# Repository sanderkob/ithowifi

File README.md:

# ithowifi
ESP based WiFi controller for Itho devices

*(note: I'm in no way a professional hardware/software engineer and have no background in these subjects. I like this for a hobby, to learn and to share my projects)*

Finished boards can be ordered in my webshop:  
[https://www.nrgwatch.nl](http://www.nrgwatch.nl)  
or in my Tindie store:  
[https://www.tindie.com/products/19680/](https://www.tindie.com/products/19680/)  

|CVE Add-on|non-CVE wifi module|
|:---:|:---:|
|  |  |

## WiFi add-on to control itho central ventilation units

-   Control your* Itho Daalderop CVE with one simple add-on module
-   No hardware changes needed to the itho box, no warranty void
-   Control the speed setting of the fan from 0 - 254 through either a simple web-interface, MQTT or WebAPI (CVE models and HRU200 only)
-   Send remote commands without having a real remote (virtual remote function)
-   Easily integrate this wifi controller in any home domotica system through MQTT or WebAPI
-   Installation can be done in minutes
-   Detailed installation manual

###  CVE Models confirmed to work:
-   CVE ECO 2 (this unit is also sold by the brand 'Heatrae Sadia' in the uk)
-   CVE ECO RFT (SE/SP, HE/HP)
-   CVE-S ECO (SE/SP, HE/HP)
-   CVE-S OPTIMA package with built-in CO2 sensor. CO2 sensor usable but an extra long pinheader needs to be soldered on the add-on)
-   HRU 200 ECO (also sold as 'Elektrodesign EHR 140 Akor BP' and 'Heatrae Sadia Advance Plus')

###  NON-CVE Models confirmed to work:
-   HRU eco fan
-   HRU 350
-   DemandFlow
-   QualityFlow
-   HeatPump WPU
-   AutoTemp

###  Models confirmed to work but modifications needed:
-   HRU 300 - see: https://github.com/arjenhiemstra/ithowifi/issues/97

####   An important note about the firmware for CVE and HRU200 devices:
The cve add-on is able to control the itho unit in standard or medium mode setting only. This means you can use the original remote but if you leave the itho box in low or high setting the itho won't accept commands from the add-on. This is itho designed behaviour. Adding a CC1101 RF module and/or letting the add-on present itself as virtual remote can circumvent this issue, the virtual remote function can also be used to force a medium mode before sending commands.

## Hardware:

A sample hardware design (KiCad) is included, this module can be plugged on the Itho main PCB directly without extra components.
The design files and BOM can be found in the hardware folder.

## Further information:

More information is available on the wiki and in the manual:
|  |  |
|---|---|
|Wiki:  |https://github.com/arjenhiemstra/ithowifi/wiki  |
|Dutch:  |https://github.com/arjenhiemstra/ithowifi/raw/master/handleiding.pdf  |
|English:  |https://github.com/arjenhiemstra/ithowifi/raw/master/manual.pdf  |

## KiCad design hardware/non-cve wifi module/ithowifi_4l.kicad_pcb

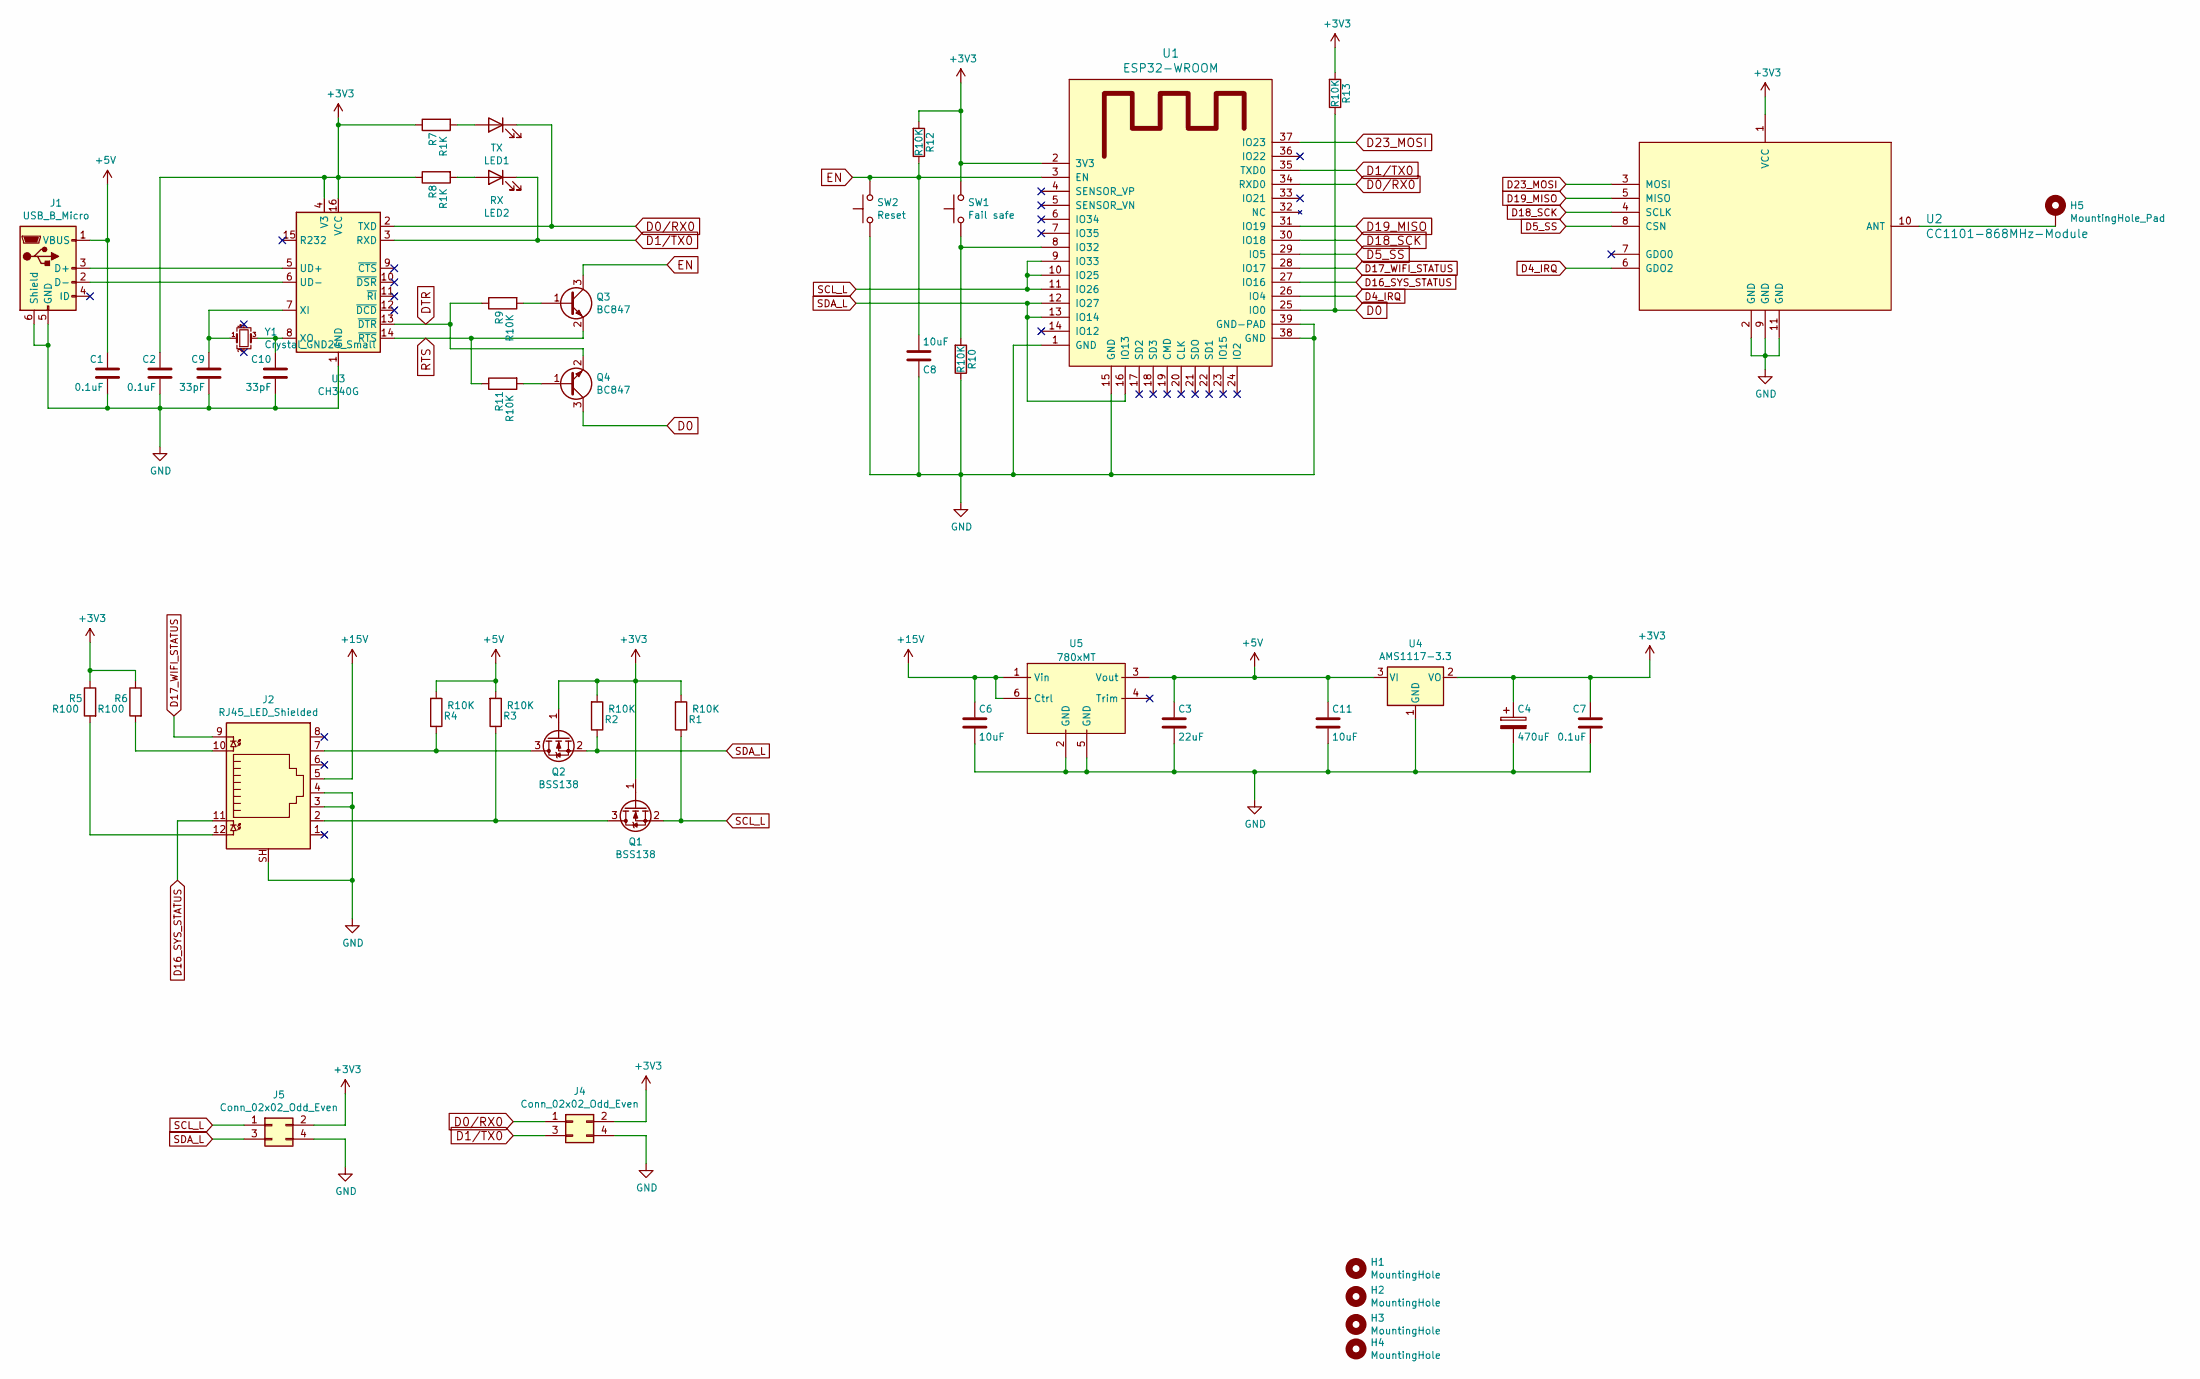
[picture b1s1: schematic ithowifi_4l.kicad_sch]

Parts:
C1, C2, C7: 0.1uF; C_0805_2012Metric
C3: 22uF; C_0805_2012Metric; LCSC C15850
C4: 470uF; CP_EIA-7343-31_Kemet-D; LCSC C7229
C6, C8, C11: 10uF; C_0805_2012Metric; LCSC C15850
C9, C10: 33pF; C_0805_2012Metric
H1, H2, H3, H4: MountingHole; MountingHole_2.5mm
H5: MountingHole_Pad; Pin_D1.0mm_L10.0mm
J1: USB_B_Micro; micro usb; LCSC C879723
J2: RJ45_LED_Shielded; RRJ45R08PC000; LCSC C386757
J4, J5: Conn_02x02_Odd_Even; PinHeader_2x02_P2.54mm_Vertical
LED1: TX; LED_0805_2012Metric; LCSC C2293
LED2: RX; LED_0805_2012Metric; LCSC C2293
Q1, Q2: BSS138; SOT-23W; LCSC C170166
Q3, Q4: BC847; SOT-23W; LCSC C6749
R1, R2, R3, R4, R9, R10, R11, R12, R13: R10K; R_0805_2012Metric; LCSC C17414
R5, R6: R100; R_0805_2012Metric; LCSC C17408
R7, R8: R1K; R_0805_2012Metric; LCSC C17513
SW1: Fail safe; TS-1187; LCSC C92589
SW2: Reset; TS-1187; LCSC C92589
U1: ESP32-WROOM; ESP32-WROOM-32E; LCSC C473012
U2: CC1101-868MHz-Module
U3: CH340G; SOIC-16_3.9x9.9mm_P1.27mm
U4: AMS1117-3.3; SOT-223-3_TabPin2
U5: 780xMT; Mornsun 780xMT; LCSC C2684892
Y1: Crystal_GND24_Small; Crystal_SMD_TXC_7M-4Pin_3.2x2.5mm

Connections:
+3V3: C2.1, C4.1, C7.1, J4.2, J5.2, Q1.1 (G), Q2.1 (G), R1.2, R2.2, R5.1, R6.1, R7.1, R8.1, R12.2, R13.2, SW1.2, U1.2 (3V3), U2.1 (VCC), U3.4 (V3), U3.16 (VCC), U4.2 (VO)
+5V: C1.1, C3.1, C11.1, J1.1 (VBUS), R3.2, R4.2, U4.3 (VI), U5.3 (Vout)
+15V: C6.1, J2.5, U5.1 (Vin), U5.6 (Ctrl)
D0: Q4.3 (C), R13.1, U1.25 (IO0)
D0/RX0: J4.1, LED1.1 (K), U1.34 (RXD0), U3.2 (TXD)
D1/TX0: J4.3, LED2.1 (K), U1.35 (TXD0), U3.3 (RXD)
D4_IRQ: U1.26 (IO4), U2.6 (GDO2)
D5_SS: U1.29 (IO5), U2.8 (CSN)
D16_SYS_STATUS: J2.11, U1.27 (IO16)
D17_WIFI_STATUS: J2.9, U1.28 (IO17)
D18_SCK: U1.30 (IO18), U2.4 (SCLK)
D19_MISO: U1.31 (IO19), U2.5 (MISO)
D23_MOSI: U1.37 (IO23), U2.3 (MOSI)
DTR: Q4.2 (E), R9.1, U3.13 (~DTR)
EN: C8.2, Q3.3 (C), R12.1, SW2.2, U1.3 (EN)
GND: C1.2, C2.2, C3.2, C4.2, C6.2, C7.2, C8.1, C9.2, C10.2, C11.2, J1.5 (GND), J1.6 (Shield), J2.3, J2.4, J2.SH, J4.4, J5.4, R10.1, SW2.1, U1.1 (GND), U1.15 (GND), U1.38 (GND), U1.39 (GND-PAD), U2.2 (GND), U2.9 (GND), U2.11 (GND), U3.1 (GND), U4.1 (GND), U5.2 (GND), U5.5 (GND)
unnamed: C9.1, U3.7 (XI), Y1.1
unnamed: C10.1, U3.8 (XO), Y1.3
unnamed: H5.1, U2.10 (ANT)
unnamed: J1.2 (D-), U3.6 (UD-)
unnamed: J1.3 (D+), U3.5 (UD+)
unnamed: J2.2, Q1.3 (D), R3.1
unnamed: J2.7, Q2.3 (D), R4.1
unnamed: J2.10, R6.2
unnamed: J2.12, R5.2
unnamed: LED1.2 (A), R7.2
unnamed: LED2.2 (A), R8.2
unnamed: Q3.1 (B), R9.2
unnamed: Q4.1 (B), R11.2
unnamed: R10.2, SW1.1, U1.8 (IO32)
RTS: Q3.2 (E), R11.1, U3.14 (~RTS)
SCL_L: J5.1, Q1.2 (S), R1.1, U1.9 (IO33), U1.10 (IO25), U1.11 (IO26)
SDA_L: J5.3, Q2.2 (S), R2.1, U1.12 (IO27), U1.13 (IO14), U1.16 (IO13)

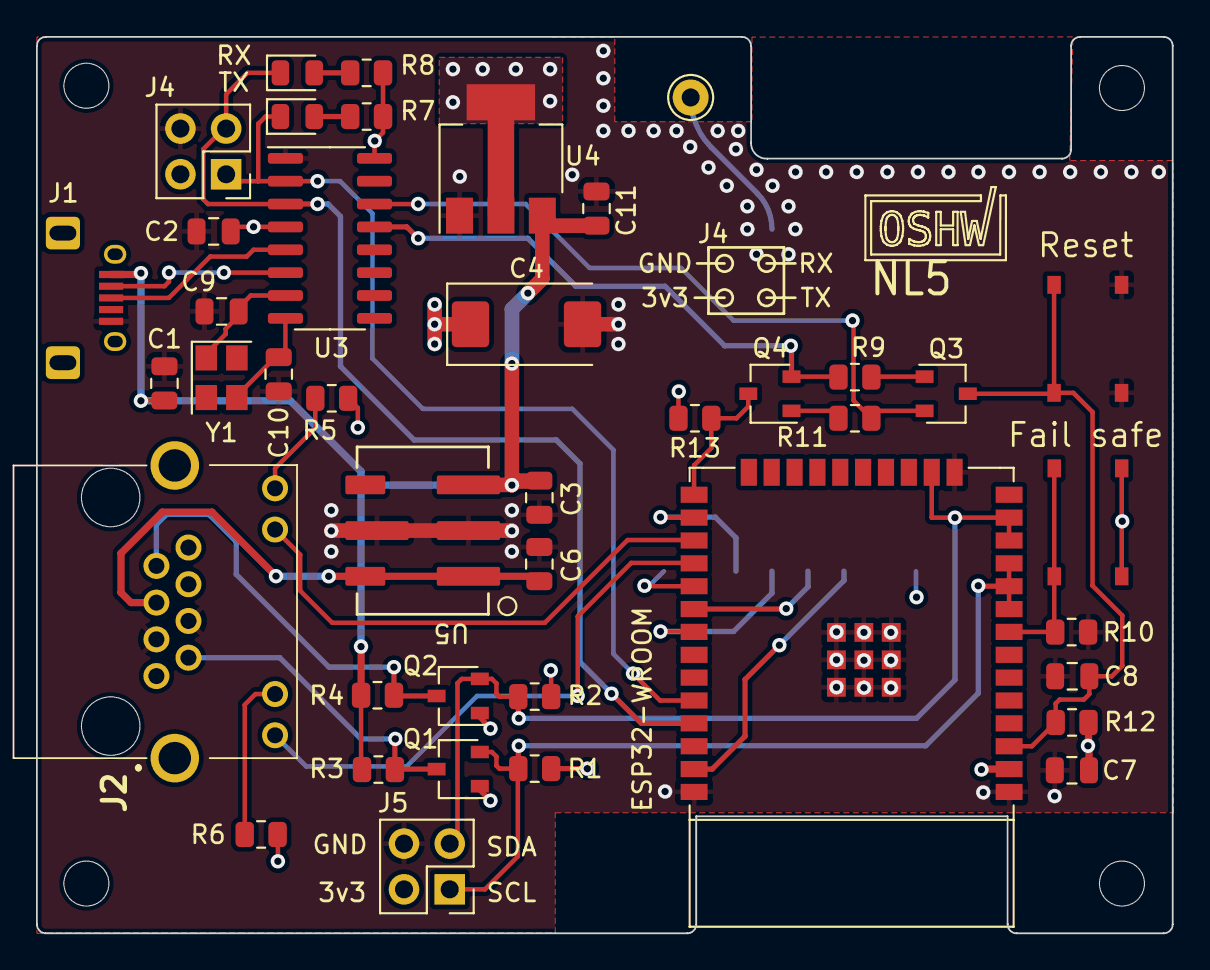
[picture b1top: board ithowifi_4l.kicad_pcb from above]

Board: 4 copper layers, 63.1 x 49.8 mm, 46 parts (1 on the bottom side), 33 nets.

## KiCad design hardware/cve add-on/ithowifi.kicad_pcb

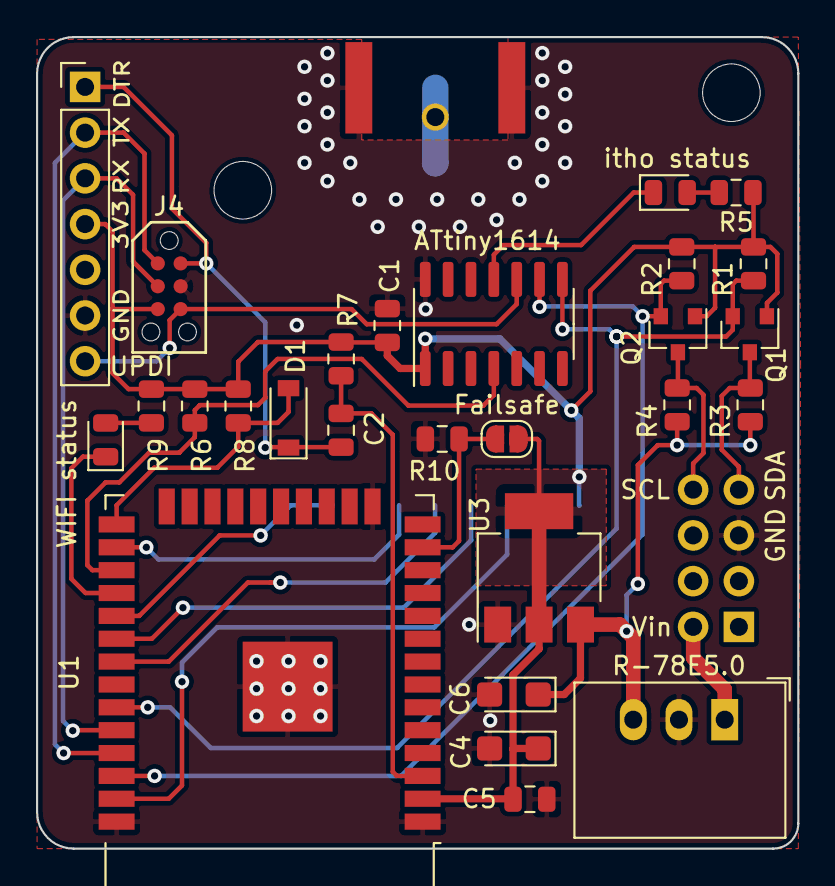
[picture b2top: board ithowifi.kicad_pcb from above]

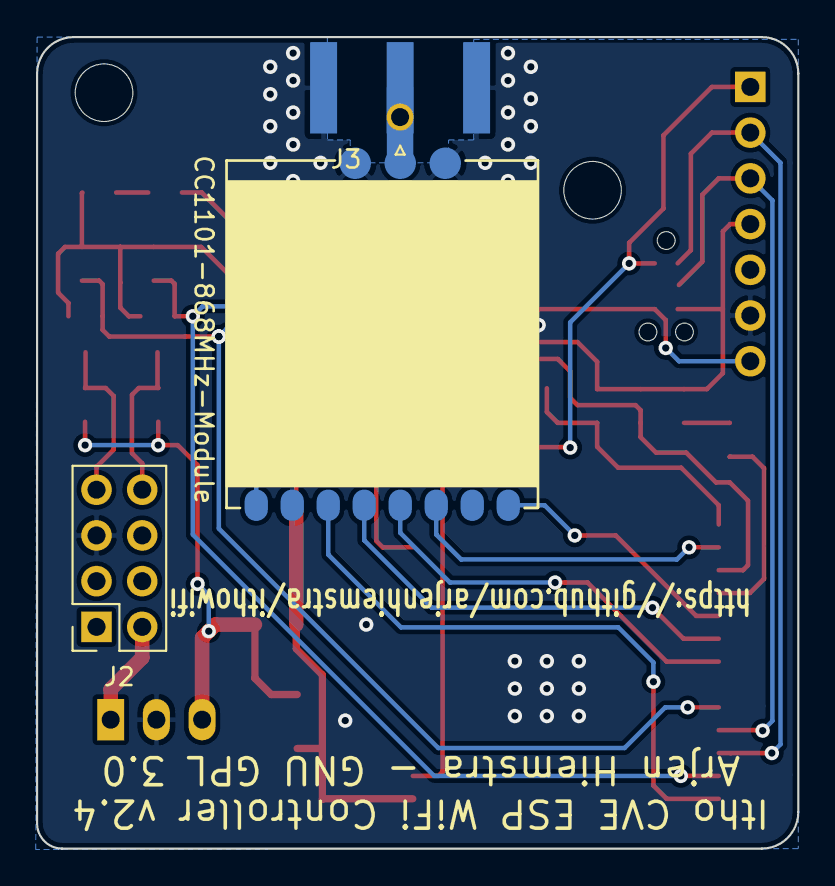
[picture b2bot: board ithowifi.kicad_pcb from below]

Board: 4 copper layers, 42.3 x 45.1 mm, 32 parts (3 on the bottom side), 26 nets.

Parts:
ATtiny1614: ATtiny1614-SS; SOIC-14_3.9x8.7mm_P1.27mm
C1: 0,1uF; L_0805_2012Metric
C2: 1uF; C_0805_2012Metric
C4, C6: 10uF; CP_EIA-3216-12_Kemet-S
C5: 0.1uF; C_0805_2012Metric
D1: D_Zener; D_SOD-123
H1, H2: MountingHole; MountingHole_2.5mm
J1: CONN_01X07; PinHeader_1x07_P2.54mm_Vertical
J2: conn; PinSocket_2x04_P2.54mm_Vertical
J3: Conn_Coaxial; SMA_Amphenol_132289_EdgeMount
J4: TC2030-MCP-NL; TC2020-MCP-NL
JP1: Failsafe; SolderJumper-2_P1.3mm_Open_RoundedPad1.0x1.5mm
LED1: WIFI status; LED_0805_2012Metric
LED2: itho status; LED_0805_2012Metric
Q1, Q2: BSS138; SOT-23
R1, R2, R3, R4, R6: R10K; R_0805_2012Metric
R5, R9: R100; R_0805_2012Metric
R7, R8, R10: 10K; R_0805_2012Metric
R-78E5.0: U2; Converter_DCDC_RECOM_R-78E-0.5_THT
U1: ESP32-WROOM; ESP32-WROOM-32
U2: CC1101-868MHz-Module
U3: AMS1117-3.3; SOT-223-3_TabPin2

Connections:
+3V3: ATtiny1614.1, C1.1, C4.1, C5.1, J1.4, J4.5, JP1.1, Q1.1, Q2.1, R1.2, R2.1, R5.1, R6.2, R7.2, R8.2, R9.1, U1.2, U2.1, U3.2
+5V: C6.1, R3.2, R4.2, R-78E5.0.3, U3.3
+16V3: J2.2, R-78E5.0.1
D0: D1.2, R8.1, U1.25
D0/RX0: J1.3, J4.3, U1.34
D1/TX0: J1.2, J4.1, U1.35
D4_IRQ: U1.26, U2.6
D5_SS: U1.29, U2.8
D18_SCK: U1.30, U2.4
D19_MISO: U1.31, U2.5
D23_MOSI: U1.37, U2.3
DTR: C2.2, D1.1, J1.1, J4.2
EN: C2.1, R7.1, U1.3
GND: ATtiny1614.14, C1.2, C4.2, C5.2, C6.2, J1.6, J2.5, J3.2, J4.4, R10.1, R-78E5.0.2, U1.1, U1.15, U1.38, U1.39, U2.2, U2.9, U2.11, U3.1
unnamed: ATtiny1614.4, R6.1, U1.27
unnamed: ATtiny1614.8, Q1.2, R1.1, U1.33
unnamed: ATtiny1614.9, Q2.2, R2.2, U1.36
unnamed: ATtiny1614.11, LED2.1
unnamed: J3.1, U2.10
unnamed: JP1.2, R10.2, U1.13
unnamed: LED1.1, U1.28
unnamed: LED1.2, R9.2
unnamed: LED2.2, R5.2
SCL: J2.8, Q2.3, R4.1
SDA: J2.7, Q1.3, R3.1
UPDI: ATtiny1614.10, J1.7, J4.6

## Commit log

2023-02-28 fix local time in logs
2023-03-08 update for final
2023-03-08 Update esp_littlefs
2023-04-06 debug CC1101
2023-04-06 2.5.4-debug
2023-04-06 debug CC1101 in CC1101.cpp
2023-04-07 timing loop readRegisterWithSyncProblem CC1101.cpp
2023-04-10 Add API support for managing settings
    This adds the ability to get and set settings using the API. Settings
    are obtained using the "getsetting" parameter, while updating settings
    is done using "setsetting" (for the index) and "value" (for the value).
    All settings that are supported can be changed through the API, instead
    of only allowing a limited subset. Due to the different settings
    supported across devices and firmware versions maintaining an allow/deny
2023-04-12 copy from werkkopie
2023-04-12 from werkkopie
2023-04-12 update from ubuntu
2023-04-12 Revert "update from ubuntu"
    This reverts commit bd9642a6314900c6f266abecf2e27b0addc2b7c8.
2023-04-12 buiuld 2.5.5-api2-tz
2023-04-20 buildb 2.5.6-ithosettings2 MQTT
2023-04-21 update E_LOG msg
2023-04-22 enabled mqtt settingstest
2023-04-22 coding Plus version
2023-04-25 upload through serial after crash in ithosettings5
2023-04-30 style: changed platformio.ini and version.h
    in platformio.ini and version.h 2.5.6-ithosettings6 is changed to 2.5.6-ithosettings7
2023-05-10 first timing mod in generic functions

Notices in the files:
hardware/cve add-on/ithowifi.kicad_pcb:
Arjen Hiemstra - GNU GPL 3.0
